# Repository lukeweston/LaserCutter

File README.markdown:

Open-hardware Arduino-compatible (Arduino Mega 2650-compatible) CNC laser cutter

Documentation goes here - when it's done.

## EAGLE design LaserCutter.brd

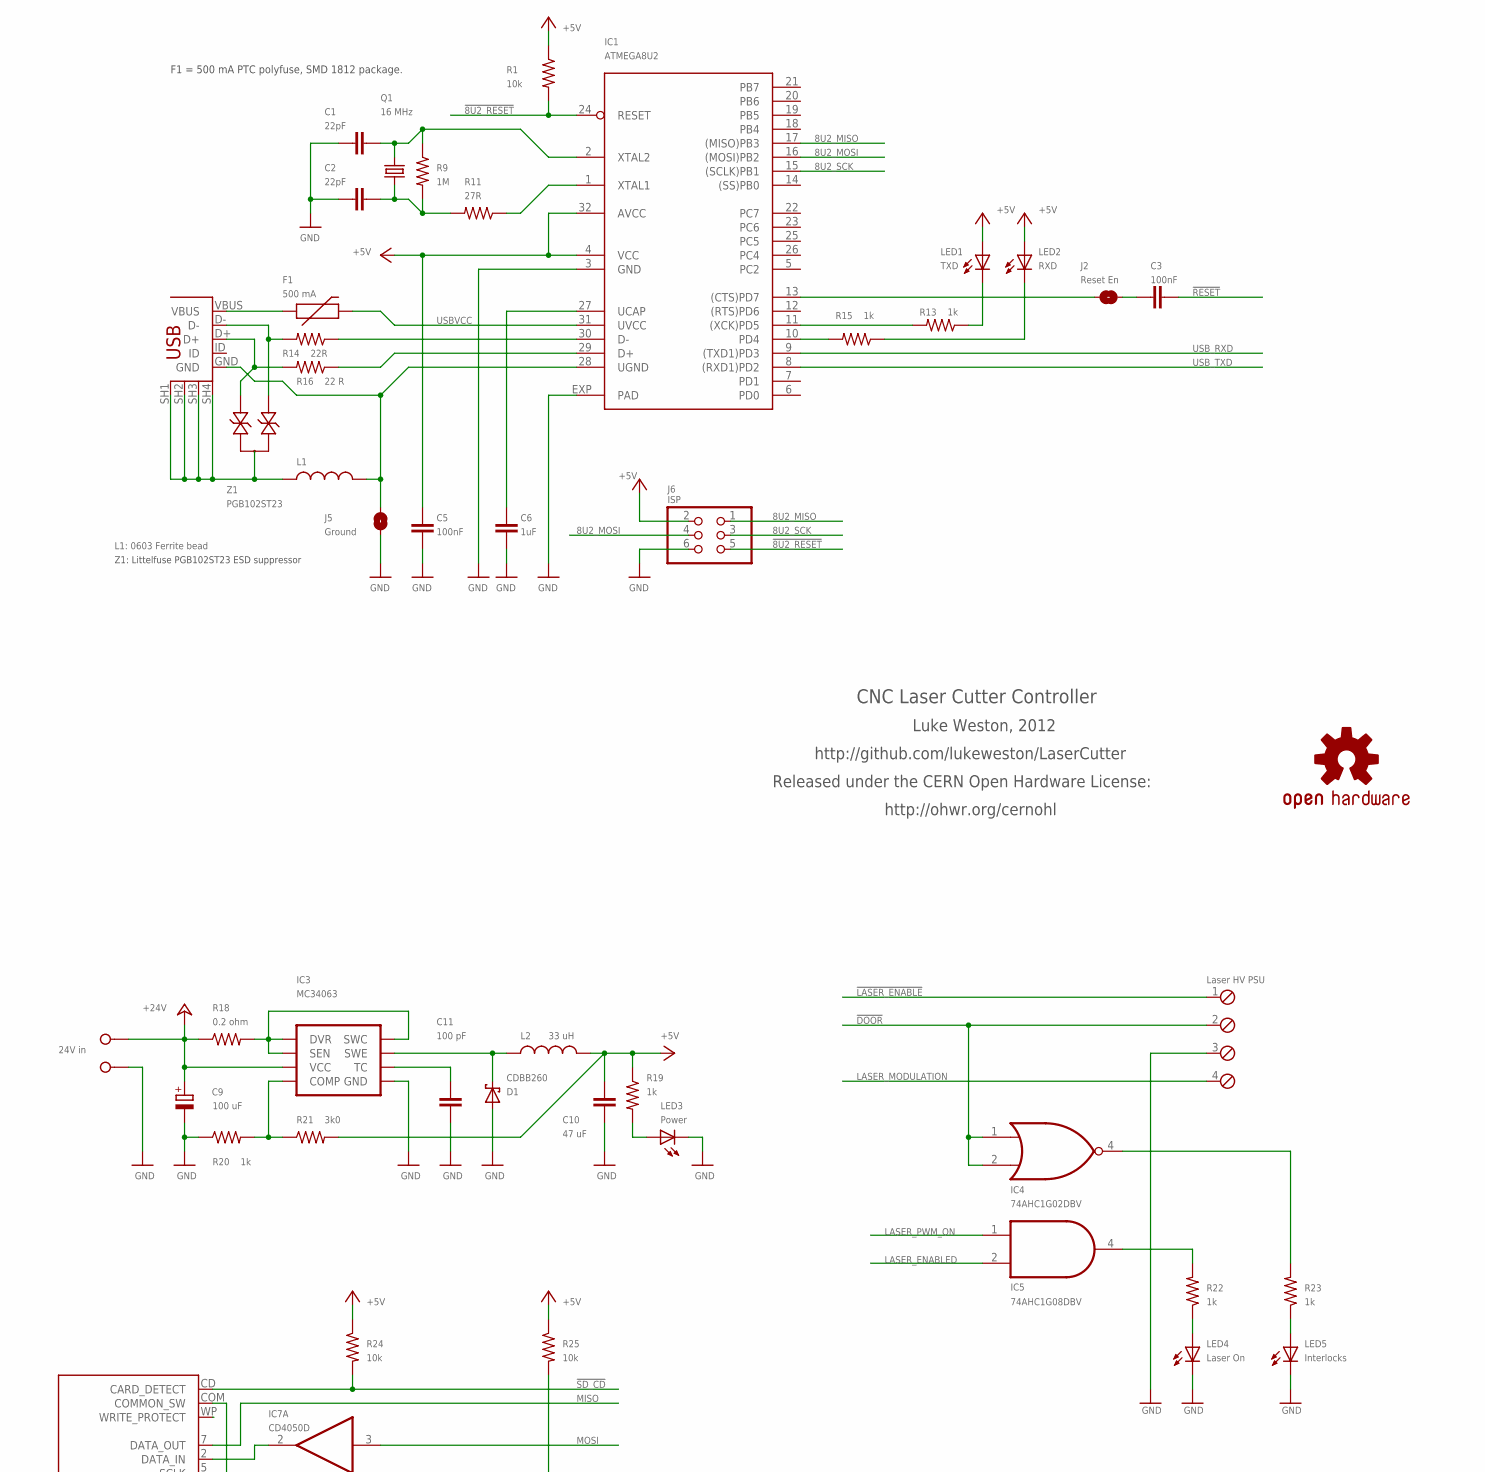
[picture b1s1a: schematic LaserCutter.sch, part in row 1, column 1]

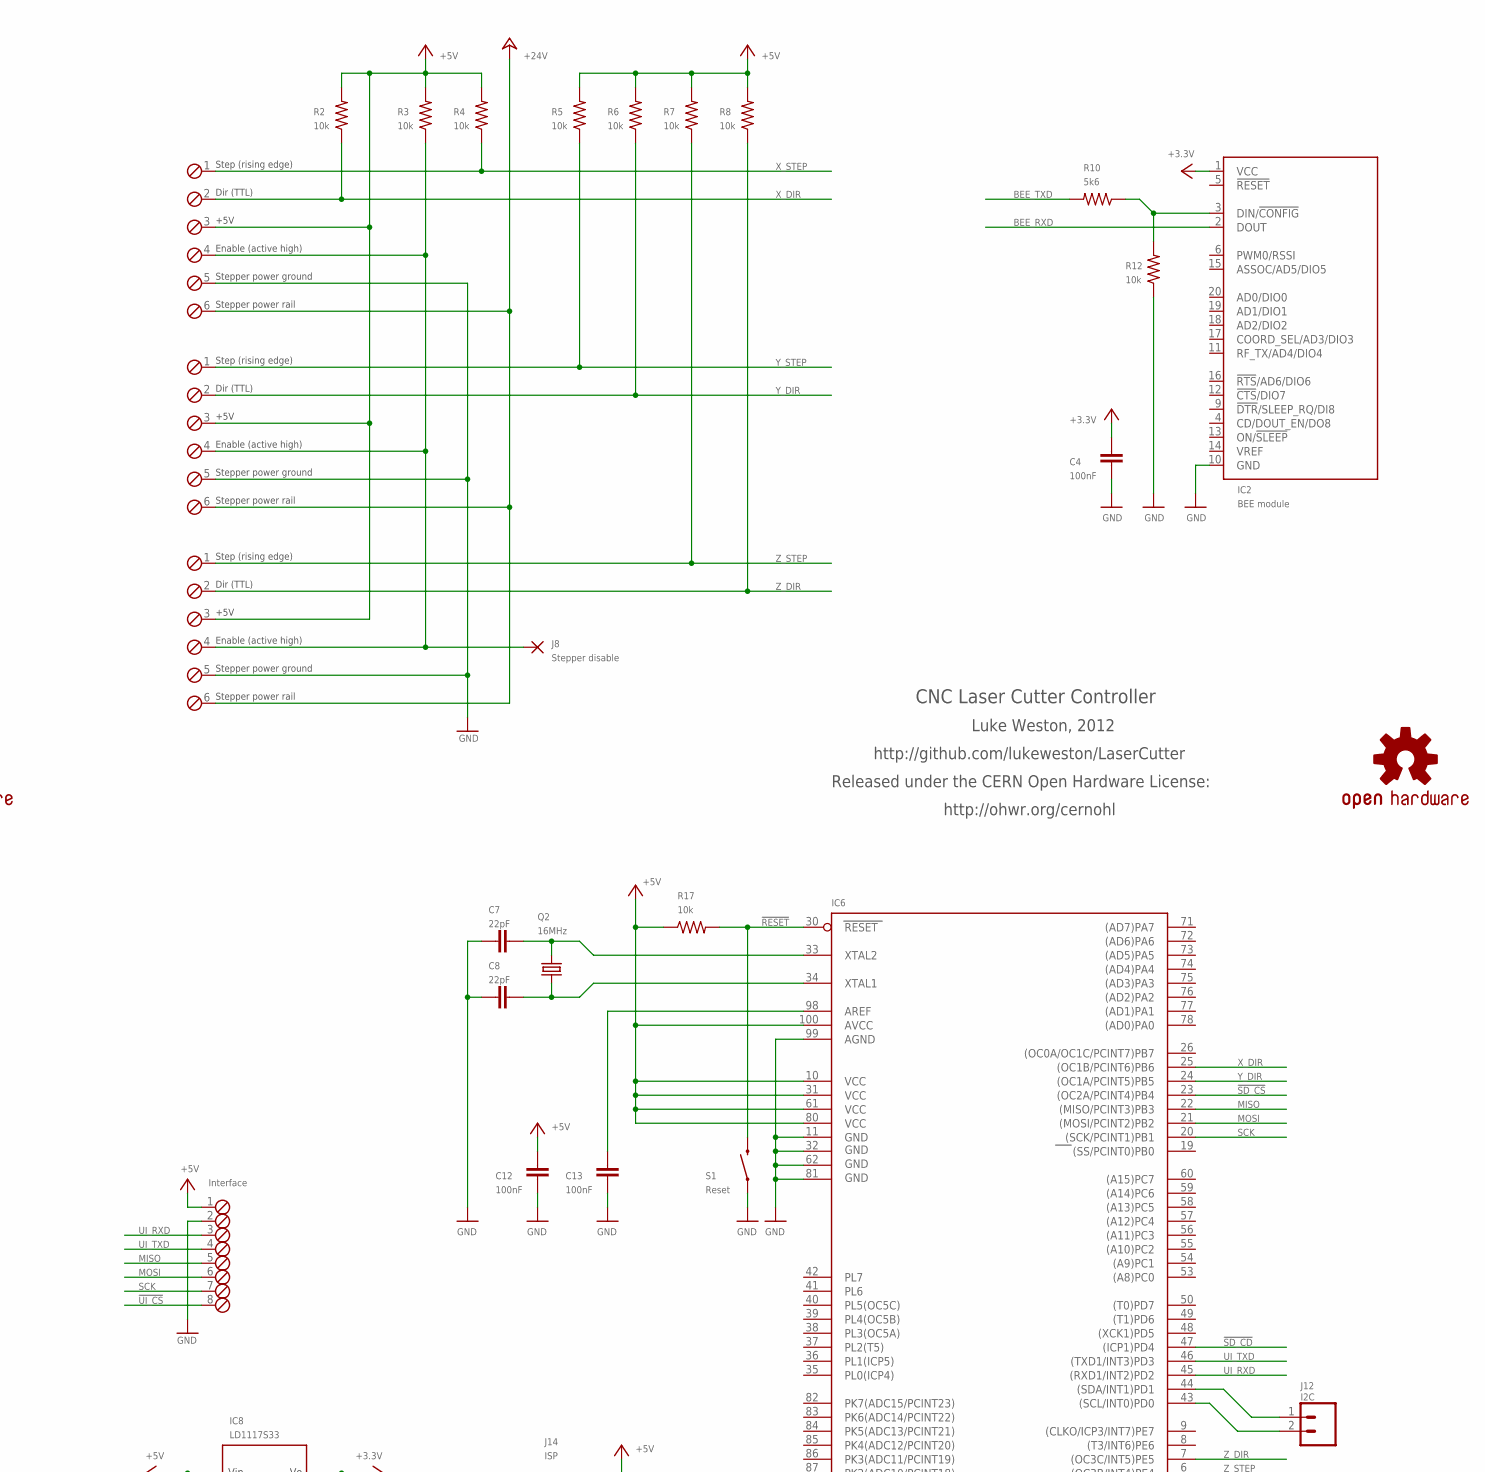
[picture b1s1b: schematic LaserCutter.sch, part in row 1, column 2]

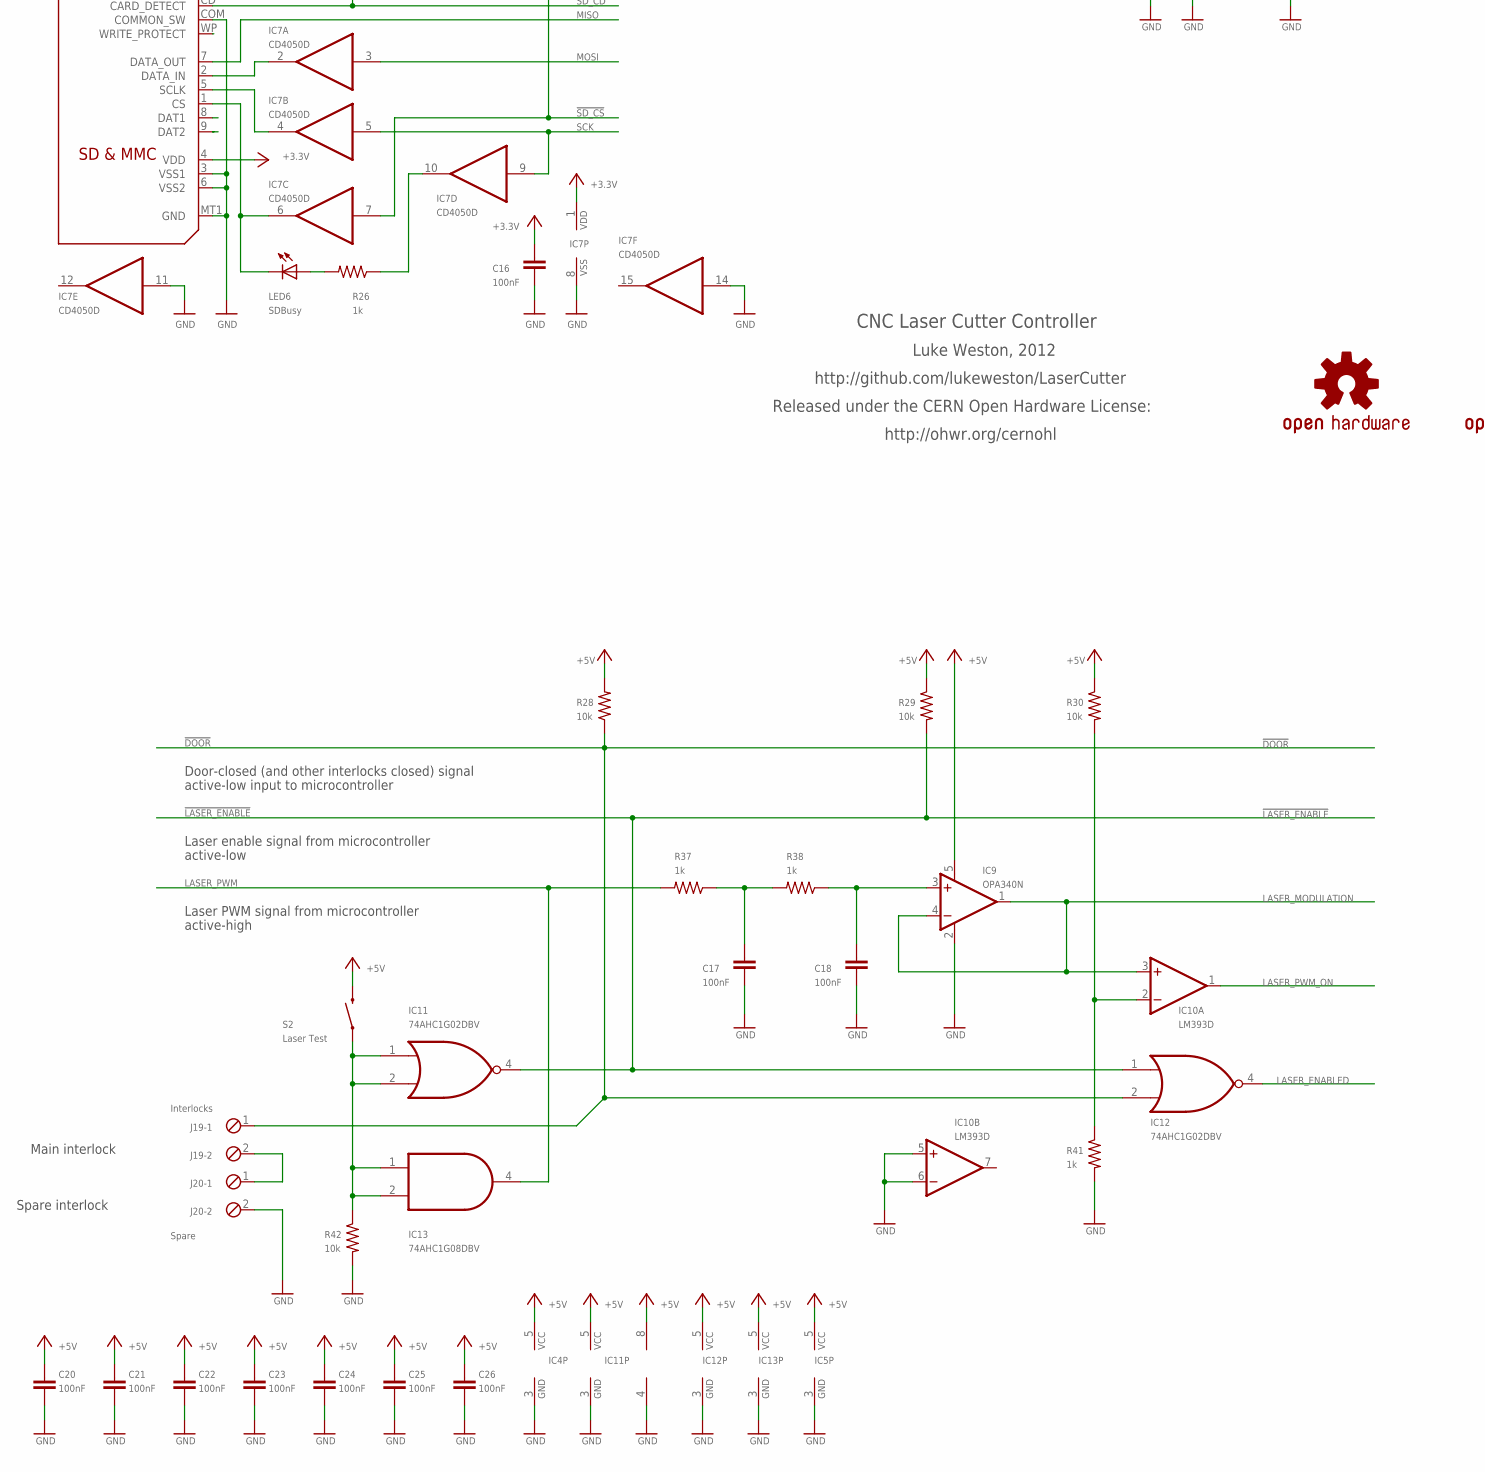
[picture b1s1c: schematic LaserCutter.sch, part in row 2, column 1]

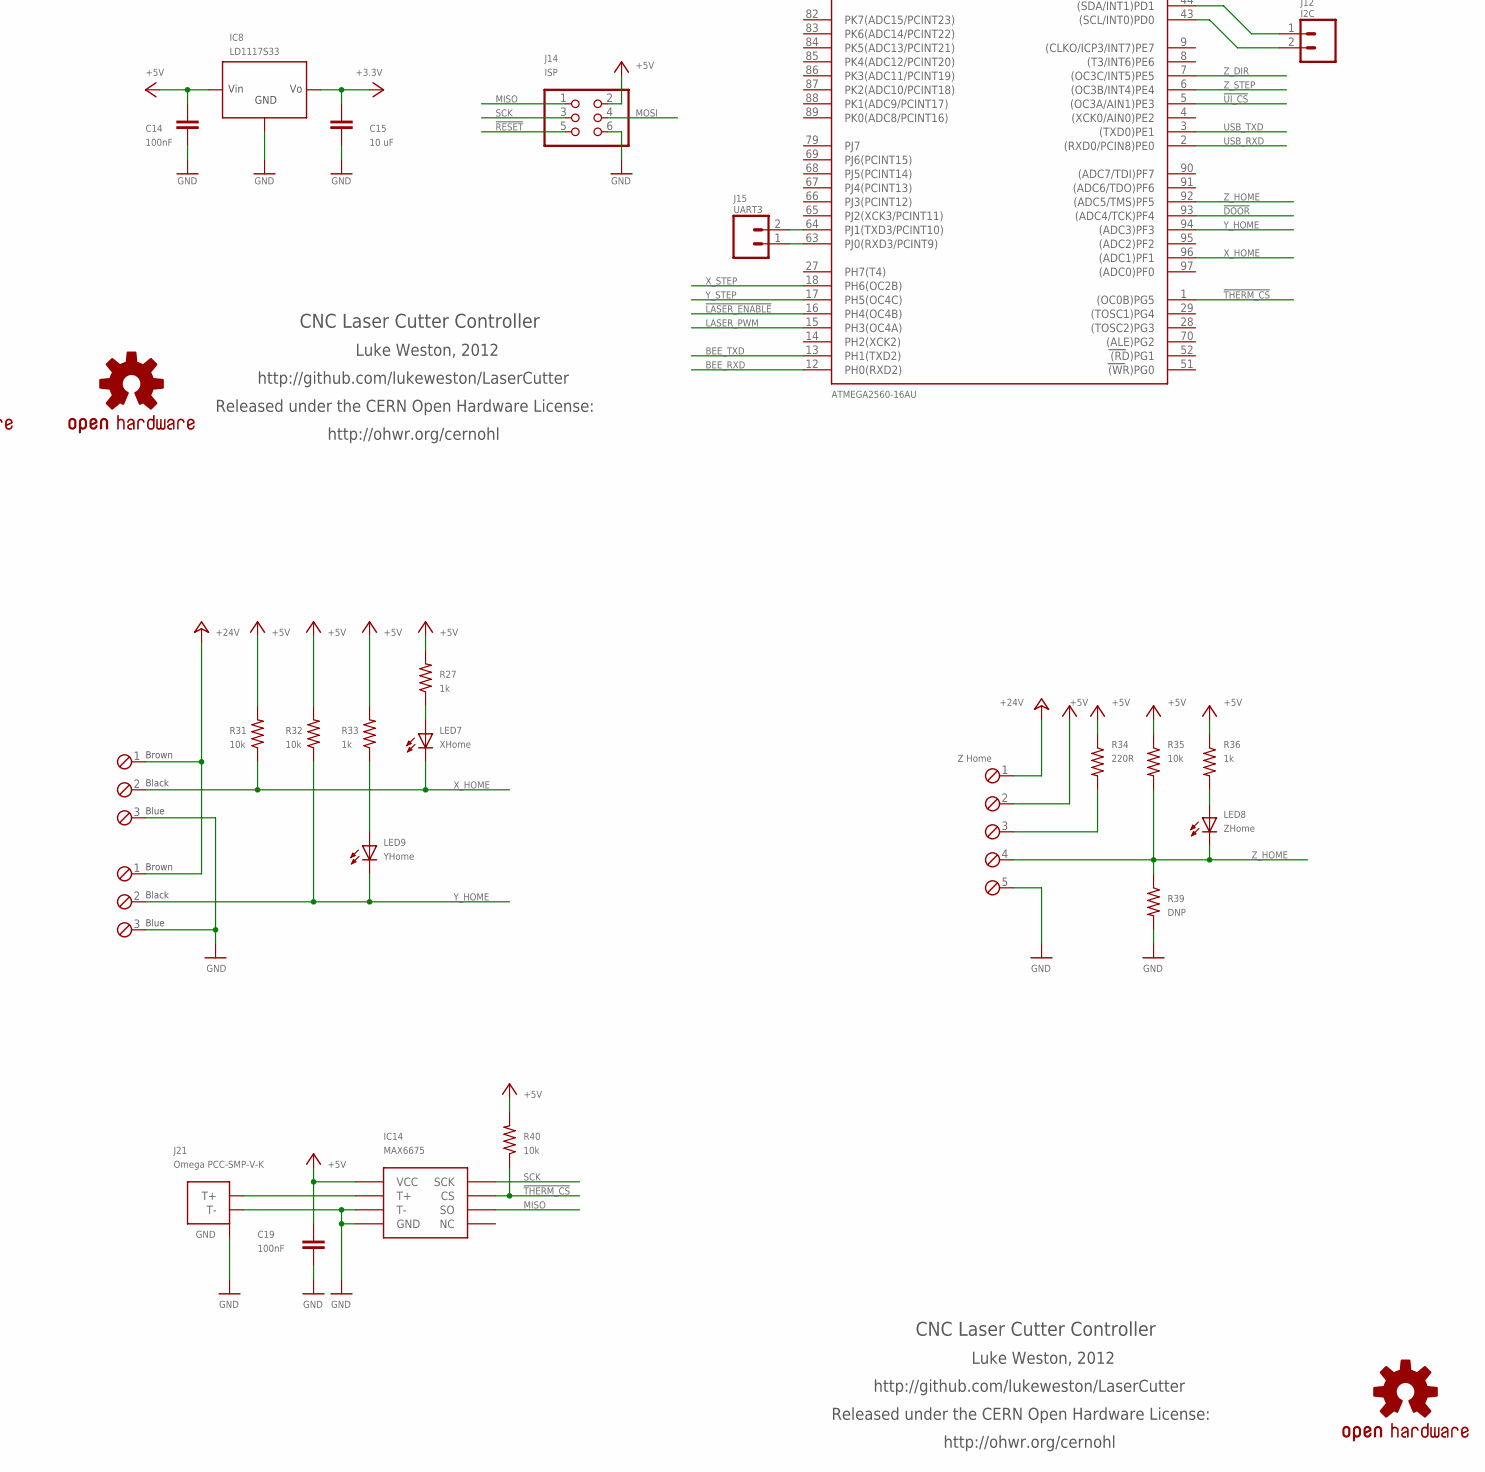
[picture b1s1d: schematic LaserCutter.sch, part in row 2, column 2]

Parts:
$1: OSHW-LOGOS; OSHW-LOGO-S
C1, C2: 22pF; 0805-LARGE
C3, C5: 100nF; 0805-LARGE
C4, C12, C13, C14, C16, C17, C18, C19, C20, C21, C22, C23, C24, C25, C26: 100nF; C0805K
C6: 1uF; 0805-LARGE
C7, C8: 22pF; C0805K
C9: 100 uF; E2,5-6
C10: 47 uF; C1210
C11: 100 pF; 0805-LARGE
C15: 10 uF; C0805K
D1: CDBB260; SMB
F1: 500 mA; 1812
IC1: ATMEGA8U2; ATMEL_QFN32
IC2: BEE module; XBEE-PRO
IC3: MC34063; SO08
IC4, IC11, IC12: 74AHC1G02DBV; SOT23-5
IC5, IC13: 74AHC1G08DBV; SOT23-5
IC6: ATMEGA2560-16AU; TQFP100
IC7: CD4050D; SO16
IC8: LD1117S33; SOT223
IC9: OPA340N; SOT23-5
IC10: LM393D; SO08
IC14: MAX6675; SOIC8-2
J1: X Stepper; 6POL254
J2: Reset En; SJ
J3: USB; USB-MINIB-FT
J4: Y Stepper; 6POL254
J5: Ground; SJ
J6, J14: ISP; 2X03
J7: Z Stepper; 6POL254
J8: Stepper disable; 1,6/0,8
J9: Laser HV PSU; 4POL254
J10: 24V in; W237-132
J11: Interface; 8POL254
J12: I2C; 1X02
J13: SDMMC18650; SDCARD
J15: UART3; 1X02
J16: X Home; 3POL254
J17: Z Home; 5POL254
J18: Y Home; 3POL254
J19: Interlocks; 2POL254
J20: Spare; 2POL254
J21: Omega PCC-SMP-V-K; PCC-SMP-V
L1: L1: 0603 Ferrite bead; 0603
L2: 33 uH; CR75
LED1: TXD; LED-0805
LED2: RXD; LED-0805
LED3: Power; LED-0805-LARGE
LED4: Laser On; LED-0805-LARGE
LED5: Interlocks; LED-0805-LARGE
LED6: SDBusy; LED-0805-LARGE
LED7: XHome; LED-0805-LARGE
LED8: ZHome; LED-0805-LARGE
LED9: YHome; LED-0805-LARGE
Q1: 16 MHz; CRYSTAL-SMD-5X3
Q2: 16MHz; CRYSTAL-SMD-5X3
R1, R17, R28: 10k; R0805
R2, R3, R4, R5, R6, R7, R8, R12, R24, R25, R29, R30, R31, R32, R35, R40, R42: 10k; M0805
R9: 1M; R0805
R10: 5k6; M0805
R11: 27R; R0805
R13, R15, R19, R20, R26: 1k; R0805
R14: 22R; R0805
R16: 22 R; R0805
R18: 0.2 ohm; R1210
R21: 3k0; R0805
R22, R23, R27, R33, R36, R37, R38, R41: 1k; M0805
R34: 220R; M0805
R39: DNP; M0805
S1: Reset; TACTILE_SWITCH_SMD
S2: Laser Test; TACTILE_SWITCH_SMD
U$, U$1, U$2, U$3: OSHW-LOGOS; OSHW-LOGO-S
Z1: PGB102ST23; SOT23-3

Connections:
8U2_MISO: IC1.17 ((MISO)PB3), J6.1
8U2_MOSI: IC1.16 ((MOSI)PB2), J6.4
8U2_SCK: IC1.15 ((SCLK)PB1), J6.3
!8U2_RESET: IC1.24 (RESET), J6.5, R1.2
!DOOR: IC4.1 (I0), IC4.2 (I1), IC6.93 ((ADC4/TCK)PF4), IC12.2 (I1), J9.2, J19.1, R28.1
!LASER_ENABLE: IC6.16 (PH4(OC4B)), IC11.4 (O), IC12.1 (I0), J9.1, R29.2
!RESET: C3.2, IC6.30 (RESET), J14.5, R17.2, S1.3 (2)
!SD_CD: IC6.47 ((ICP1)PD4), J13.CD (CARD_DETECT), R24.2
!SD_CS: IC6.23 ((OC2A/PCINT4)PB4), IC7.7 (I), R25.2
!THERM_CS: IC6.1 ((OC0B)PG5), IC14.6 (CS), R40.1
!UI_CS: IC6.5 ((OC3A/AIN1)PE3), J11.8
+3V3: C4.1, C15.1, C16.1, IC2.1 (VCC), IC7.1 (VDD), IC8.2 (VOUT), J13.4 (VDD)
+5V: C5.1, C10.1, C12.2, C14.1, C19.1, C20.1, C21.1, C22.1, C23.1, C24.1, C25.1, C26.1, IC1.4 (VCC), IC1.32 (AVCC), IC4.5 (VCC), IC5.5 (VCC), IC6.10 (VCC), IC6.31 (VCC1), IC6.61 (VCC2), IC6.80 (VCC3), IC6.100 (AVCC), IC8.3 (VIN), IC9.5 (V+), IC10.8 (V+), IC11.5 (VCC), IC12.5 (VCC), IC13.5 (VCC), IC14.4 (VCC), J1.3, J4.3, J6.2, J7.3, J11.1, J14.2, J17.2, L2.P$2 (2), LED1.A, LED2.A, R1.1, R2.2, R3.2, R4.2, R5.2, R6.2, R7.2, R8.2, R17.1, R19.1, R21.2, R24.1, R25.1, R27.2, R28.2, R29.1, R30.1, R31.2, R32.2, R33.2, R34.1, R35.1, R36.1, R40.2, S2.3 (2)
+24V: C9.+, IC3.6 (VCC), J1.6, J4.6, J7.6, J10.1, J16.1, J17.1, J18.1, R18.1
BEE_RXD: IC2.2 (DOUT), IC6.12 (PH0(RXD2))
BEE_TXD: IC6.13 (PH1(TXD2)), R10.2
DAT1: J13.8 (DAT1)
DAT2: J13.9 (DAT2)
GND: C1.1, C2.1, C4.2, C5.2, C6.2, C7.1, C8.1, C9.-, C10.2, C11.2, C12.1, C13.1, C14.2, C15.2, C16.2, C17.2, C18.2, C19.2, C20.2, C21.2, C22.2, C23.2, C24.2, C25.2, C26.2, D1.A, IC1.3 (GND), IC1.EXP (PAD), IC2.10 (GND), IC3.4 (GND), IC4.3 (GND), IC5.3 (GND), IC6.11 (GND), IC6.32 (GND1), IC6.62 (GND2), IC6.81 (GND3), IC6.99 (AGND), IC7.8 (VSS), IC7.11 (I), IC7.14 (I), IC8.1 (GND), IC9.2 (V-), IC10.4 (V-), IC10.5 (+IN), IC10.6 (-IN), IC11.3 (GND), IC12.3 (GND), IC13.3 (GND), IC14.1 (GND), IC14.2 (T-), J1.5, J4.5, J5.2, J6.6, J7.5, J9.3, J10.2, J11.2, J13.3 (VSS1), J13.6 (VSS2), J13.COM (COMMON_SW), J13.MT1 (GND), J14.6, J16.3, J17.5, J18.3, J20.2, J21.P$1 (GND), J21.P$2 (GND), J21.T-, LED3.C, LED4.C, LED5.C, R12.1, R20.1, R39.2, R41.2, R42.2, S1.1
J81: J1.4, J4.4, J7.4, J8.1, R3.1
LASER_ENABLED: IC5.2 (I1), IC12.4 (O)
LASER_MODULATION: IC9.1 (OUT), IC9.4 (-IN), IC10.3 (+IN), J9.4
LASER_PWM: IC6.15 (PH3(OC4A)), IC13.4 (O), R37.2
LASER_PWM_ON: IC5.1 (I0), IC10.1 (OUT)
MISO: IC6.22 ((MISO/PCINT3)PB3), IC14.7 (SO), J11.5, J13.7 (DATA_OUT), J14.1
MOSI: IC6.21 ((MOSI/PCINT2)PB2), IC7.3 (I), J11.6, J14.4
unnamed: IC7.2 (O), J13.2 (DATA_IN)
unnamed: LED3.A, R19.2
unnamed: C7.2, IC6.33 (XTAL2), Q2.3 (2)
unnamed: IC2.3 (DIN/!CONFIG), R10.1, R12.2
unnamed: IC1.28 (UGND), J3.GND, J5.1, L1.2
unnamed: IC11.1 (I0), IC11.2 (I1), IC13.1 (I0), IC13.2 (I1), R42.1, S2.1
unnamed: IC3.1 (SWC), IC3.7 (SEN), IC3.8 (DVR), R18.2
unnamed: IC7.4 (O), J13.5 (SCLK)
unnamed: LED6.A, R26.2
unnamed: C11.1, IC3.3 (TC)
unnamed: J19.2, J20.1
unnamed: IC3.5 (COMP), R20.2, R21.1
unnamed: LED8.A, R36.2
unnamed: IC10.2 (-IN), R30.2, R41.1
unnamed: IC7.10 (O), R26.1
unnamed: IC7.6 (O), J13.1 (CS), LED6.C
unnamed: D1.C, IC3.2 (SWE), L2.P$1 (1)
unnamed: IC5.4 (O), R22.2
unnamed: LED4.A, R22.1
unnamed: C18.1, IC9.3 (+IN), R38.1
unnamed: IC14.3 (T+), J21.T+
unnamed: C17.1, R37.1, R38.2
unnamed: IC4.4 (O), R23.2
unnamed: LED9.A, R33.1
unnamed: LED5.A, R23.1
unnamed: LED7.A, R27.1
unnamed: J17.3, R34.2
unnamed: C8.2, IC6.34 (XTAL1), Q2.1
unnamed: C13.2, IC6.98 (AREF)
unnamed: C1.2, IC1.2 (XTAL2), Q1.3 (2), R9.1
unnamed: IC1.1 (XTAL1), R11.1
unnamed: C2.2, Q1.1, R9.2, R11.2
unnamed: F1.1, J3.VBUS
unnamed: J3.D+, R16.2, Z1.2
unnamed: C6.1, IC1.27 (UCAP)
unnamed: J3.D-, R14.2, Z1.1
unnamed: IC1.30 (D-), R14.1
unnamed: IC1.29 (D+), R16.1
unnamed: LED2.C, R15.1
unnamed: C3.1, J2.2
unnamed: IC1.13 ((CTS)PD7), J2.1
unnamed: IC1.11 ((XCK)PD5), R13.2
unnamed: IC1.10 (PD4), R15.2
unnamed: LED1.C, R13.1
unnamed: J3.SH1 (SH$1), J3.SH2 (SH$2), J3.SH3 (SH$3), J3.SH4 (SH$4), L1.1, Z1.3
RXD3: IC6.63 (PJ0(RXD3/PCINT9)), J15.1
SCK: IC6.20 ((SCK/PCINT1)PB1), IC7.5 (I), IC7.9 (I), IC14.5 (SCK), J11.7, J14.3
SCL: IC6.43 ((SCL/INT0)PD0), J12.2
SDA: IC6.44 ((SDA/INT1)PD1), J12.1
TXD3: IC6.64 (PJ1(TXD3/PCINT10)), J15.2
UI_RXD: IC6.45 ((RXD1/INT2)PD2), J11.3
UI_TXD: IC6.46 ((TXD1/INT3)PD3), J11.4
USBVCC: F1.2, IC1.31 (UVCC)
USB_RXD: IC1.9 ((TXD1)PD3), IC6.2 ((RXD0/PCIN8)PE0)
USB_TXD: IC1.8 ((RXD1)PD2), IC6.3 ((TXD0)PE1)
WP: J13.WP (WRITE_PROTECT)
X_DIR: IC6.25 ((OC1B/PCINT6)PB6), J1.2, R2.1
X_HOME: IC6.96 ((ADC1)PF1), J16.2, LED7.C, R31.1
X_STEP: IC6.18 (PH6(OC2B)), J1.1, R4.1
Y_DIR: IC6.24 ((OC1A/PCINT5)PB5), J4.2, R6.1
Y_HOME: IC6.94 ((ADC3)PF3), J18.2, LED9.C, R32.1
Y_STEP: IC6.17 (PH5(OC4C)), J4.1, R5.1
Z_DIR: IC6.7 ((OC3C/INT5)PE5), J7.2, R8.1
Z_HOME: IC6.92 ((ADC5/TMS)PF5), J17.4, LED8.C, R35.2, R39.1
Z_STEP: IC6.6 ((OC3B/INT4)PE4), J7.1, R7.1

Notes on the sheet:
Z1: Littelfuse PGB102ST23 ESD suppressor
F1 = 500 mA PTC polyfuse, SMD 1812 package.
Step (rising edge)
Dir (TTL)
+5V
Enable (active high)
Stepper power ground
Stepper power rail
Brown
Black
Blue
Main interlock
Spare interlock
Laser PWM signal from microcontroller
active-high
Laser enable signal from microcontroller
active-low
Door-closed (and other interlocks closed) signal
active-low input to microcontroller
CNC Laser Cutter Controller
Luke Weston, 2012
http://github.com/lukeweston/LaserCutter
Released under the CERN Open Hardware License:
http://ohwr.org/cernohl

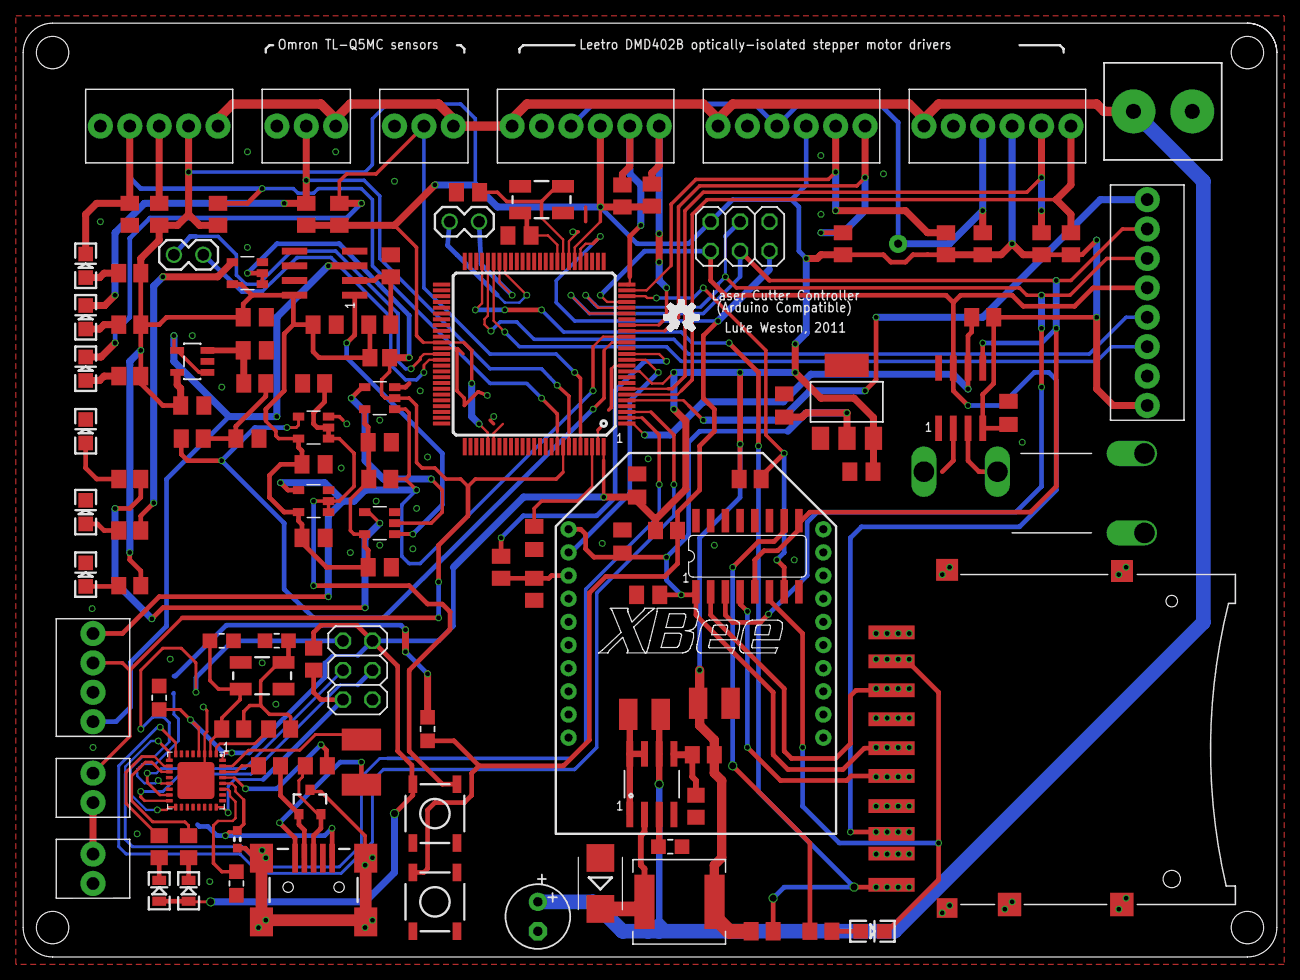
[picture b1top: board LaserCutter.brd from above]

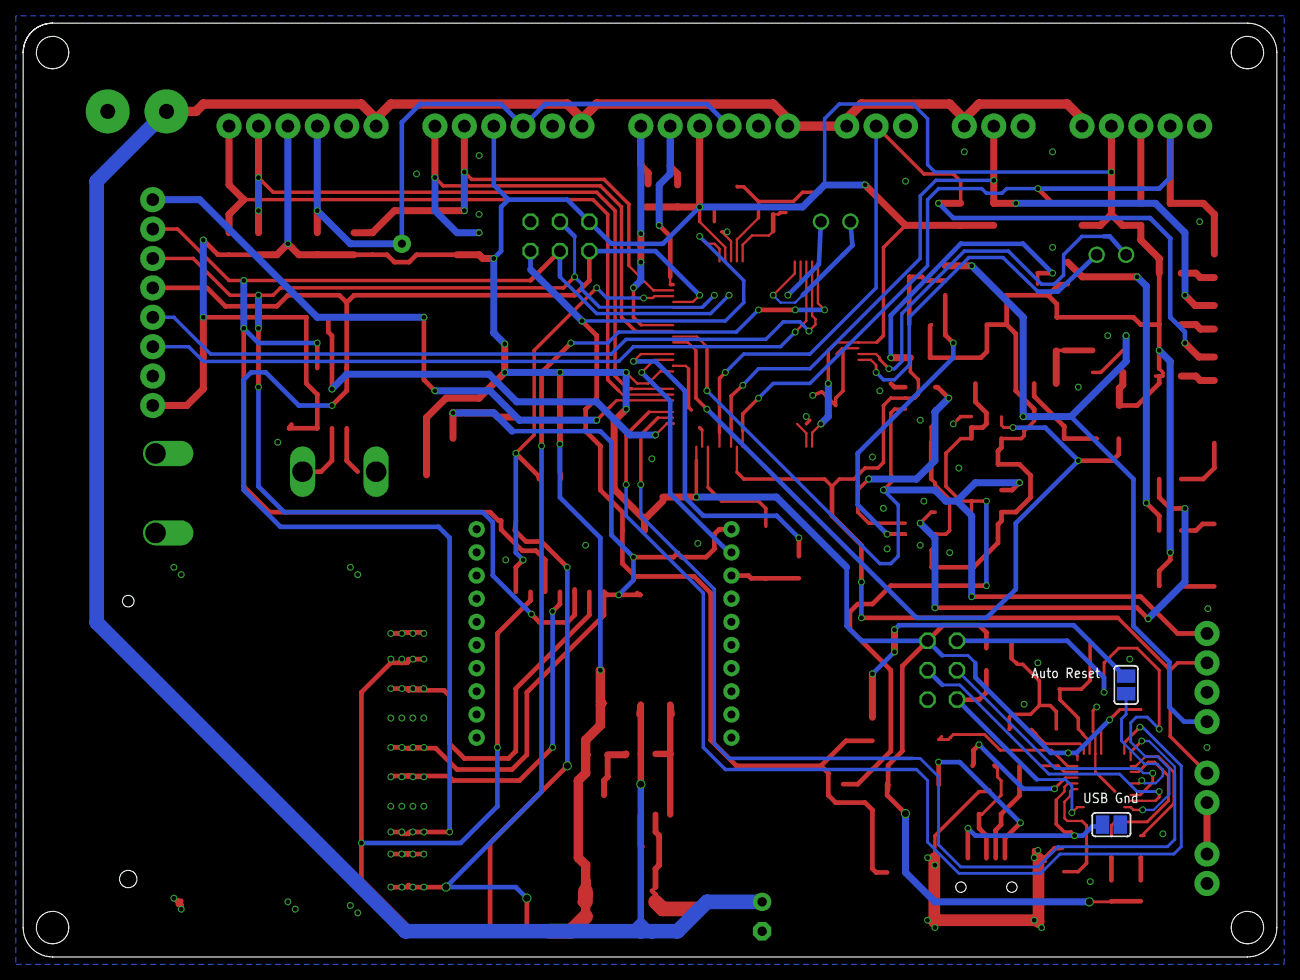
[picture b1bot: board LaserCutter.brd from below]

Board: 2 copper layers, 108.3 x 80.6 mm, 126 parts (2 on the bottom side), 88 nets.

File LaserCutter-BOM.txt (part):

Partlist

Exported from LaserCutter.sch at 5/04/12 11:44 PM

EAGLE Version 5.11.0 Copyright (c) 1988-2010 CadSoft

Part     Value             Device                Package            Library               Sheet

C1       22pF              CAP0805-LARGE         0805-LARGE         freetronics-marc      1
C2       22pF              CAP0805-LARGE         0805-LARGE         freetronics-marc      1
C3       100nF             CAP0805-LARGE         0805-LARGE         freetronics-marc      1
C4       100nF             C-EUC0805K            C0805K             rcl                   1
C5       100nF             CAP0805-LARGE         0805-LARGE         freetronics-marc      1
C6       1uF               CAP0805-LARGE         0805-LARGE         freetronics-master-v1 1
C7       22pF              C-EUC0805K            C0805K             rcl                   1
C8       22pF              C-EUC0805K            C0805K             rcl                   1
C9       100nF             CAP0805-LARGE         0805-LARGE         freetronics-master-v1 1
C10      47uF 35V          CPOL-EUSMCE           SMC_E              rcl                   1
C11      100uF             CPOL-EUSMCC           SMC_C              rcl                   1
C12      3.3nF             CAP0805-LARGE         0805-LARGE         freetronics-master-v1 1
C13      100nF             C-EUC0805K            C0805K             rcl                   1
C14      100nF             C-EUC0805K            C0805K             rcl                   1
C15      100nF             C-EUC0805K            C0805K             rcl                   1
C16      10uF              CPOL-EUSMCA           SMC_A              rcl                   1
C17      100nF             C-EUC0805K            C0805K             rcl                   1
C18      100nF             C-EUC0805K            C0805K             rcl                   1
C19      100nF             C-EUC0805K            C0805K             rcl                   1
C20      100nF             C-EUC0805K            C0805K             rcl                   1
C21      100nF             C-EUC0805K            C0805K             rcl                   1
C22      100nF             C-EUC0805K            C0805K             rcl                   1
C23      100nF             C-EUC0805K            C0805K             rcl                   1
C24      100nF             C-EUC0805K            C0805K             rcl                   1
C25      100nF             C-EUC0805K            C0805K             rcl                   1
C26      100nF             C-EUC0805K            C0805K             rcl                   1
C27      100nF             C-EUC0805K            C0805K             rcl                   1
D1       1N914             DIODE-SOD323-W        SOD323-W           diode                 1
D2       1N5819            DIODE-SOD123          SOD123             diode                 1
F1       500 mA            PTC1812               1812               EtherMega2            1
IC1      ATMEGA8U2         ATMEL_ATMEGA8U2-MUQFN ATMEL_QFN32        freetronics-jon       1
IC2      BEE module        XBEE                  XBEE-PRO           Luke                  1
IC3      LT1376-5          LT1375                SOIC8              Luke                  1
IC4      74AHC1G02DBV      74AHC1G02DBV          SOT23-5            74xx-little-us        1
IC5      74AHC1G08DBV      74AHC1G08DBV          SOT23-5            74xx-little-us        1
IC6      ATMEGA2560-16AU   ATMEGA1280-16AU       TQFP100            atmel-2005            1
IC7      CD4050D           4050D                 SO16               40xx                  1
IC8      LD1117S33         REG1117               SOT223             burr-brown            1
IC9      OPA340N           OPA340N               SOT23-5            burr-brown            1
IC10     LM393D            LM393D                SO08               linear                1
IC11     74AHC1G02DBV      74AHC1G02DBV          SOT23-5            74xx-little-us        1
IC12     74AHC1G02DBV      74AHC1G02DBV          SOT23-5            74xx-little-us        1
IC13     74AHC1G08DBV      74AHC1G08DBV          SOT23-5            74xx-little-us        1
IC14     MAX6675           MAX6675               SOIC8-2            Thermocouple          1
J1       X Stepper         MPT6                  6POL254            con-phoenix-254       1
J2       DFU               1,6/0,8               1,6/0,8            wirepad               1
J3       USB               USB-FT                USB-MINIB-FT       freetronics-master-v1 1
J4       Y Stepper         MPT6                  6POL254            con-phoenix-254       1
J5       ISP               AVR_SPI_PRG_6NS       2X3-NS             SparkFun              1
J6       Z Stepper         MPT6                  6POL254            con-phoenix-254       1
J7       Stepper disable   1,6/0,8               1,6/0,8            wirepad               1
J8       Laser HV PSU      MPT4                  4POL254            con-phoenix-254       1
J9       24V in            W237-02P              W237-132           con-wago-508          1
J10      Interface         MPT8                  8POL254            con-phoenix-254       1
J11      ISP               AVR_SPI_PRG_6NS       2X3-NS             SparkFun              1
J12      I2C               PINHD-1X2             1X02               pinhead               1
J13      SDMMC18650        SDMMC18650            SDCARD             adafruit              1
J14      UART3             PINHD-1X2             1X02               pinhead               1
J15      X Home            MPT3                  3POL254            con-phoenix-254       1
J16      Z Home            MPT5                  5POL254            con-phoenix-254       1
J17      Y Home            MPT3                  3POL254            con-phoenix-254       1
J18      Interlocks        MPT2                  2POL254            con-phoenix-254       1
J19      Spare             MPT2                  2POL254            con-phoenix-254       1
J20      Omega PCC-SMP-V-K TC_JACK               TC_JACK            Thermocouple          1
J21      Ground            SJ                    SJ                 jumper                1
J22      Reset En          SJ                    SJ                 jumper                1
L1       L                 INDUCTOR0603          0603               freetronics-master-v1 1
L2       10uH              INDUCTORCR75          CR75               SparkFun              1
LED1     TXD               LED0805               LED-0805           freetronics           1
LED2     RXD               LED0805               LED-0805           freetronics           1
LED3     Power             LED0805-LARGE         LED-0805-LARGE     freetronics           1
LED4     Laser On          LED0805-LARGE         LED-0805-LARGE     freetronics           1
LED5     Interlocks        LED0805-LARGE         LED-0805-LARGE     freetronics           1
LED6     SDBusy            LED0805-LARGE         LED-0805-LARGE     freetronics           1
LED7     XHome             LED0805-LARGE         LED-0805-LARGE     freetronics           1
LED8     ZHome             LED0805-LARGE         LED-0805-LARGE     freetronics           1
LED9     YHome             LED0805-LARGE         LED-0805-LARGE     freetronics           1
Q1       16 MHz            CRYSTAL5X3            CRYSTAL-SMD-5X3    SparkFun              1
Q2       16MHz             CRYSTAL5X3            CRYSTAL-SMD-5X3    SparkFun              1
R1       10k               R-US_R0805            R0805              rcl                   1
R2       10k               R-US_M0805            M0805              resistor              1
R3       10k               R-US_M0805            M0805              resistor              1
R4       10k               R-US_M0805            M0805              resistor              1
R5       10k               R-US_M0805            M0805              resistor              1
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
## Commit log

2012-04-05 reworked SPI interface
2012-05-03 changed to cheaper MC34063 buck converter
2012-05-13 fixed terminal block PCB footprints
2012-07-18 a few tweaks
